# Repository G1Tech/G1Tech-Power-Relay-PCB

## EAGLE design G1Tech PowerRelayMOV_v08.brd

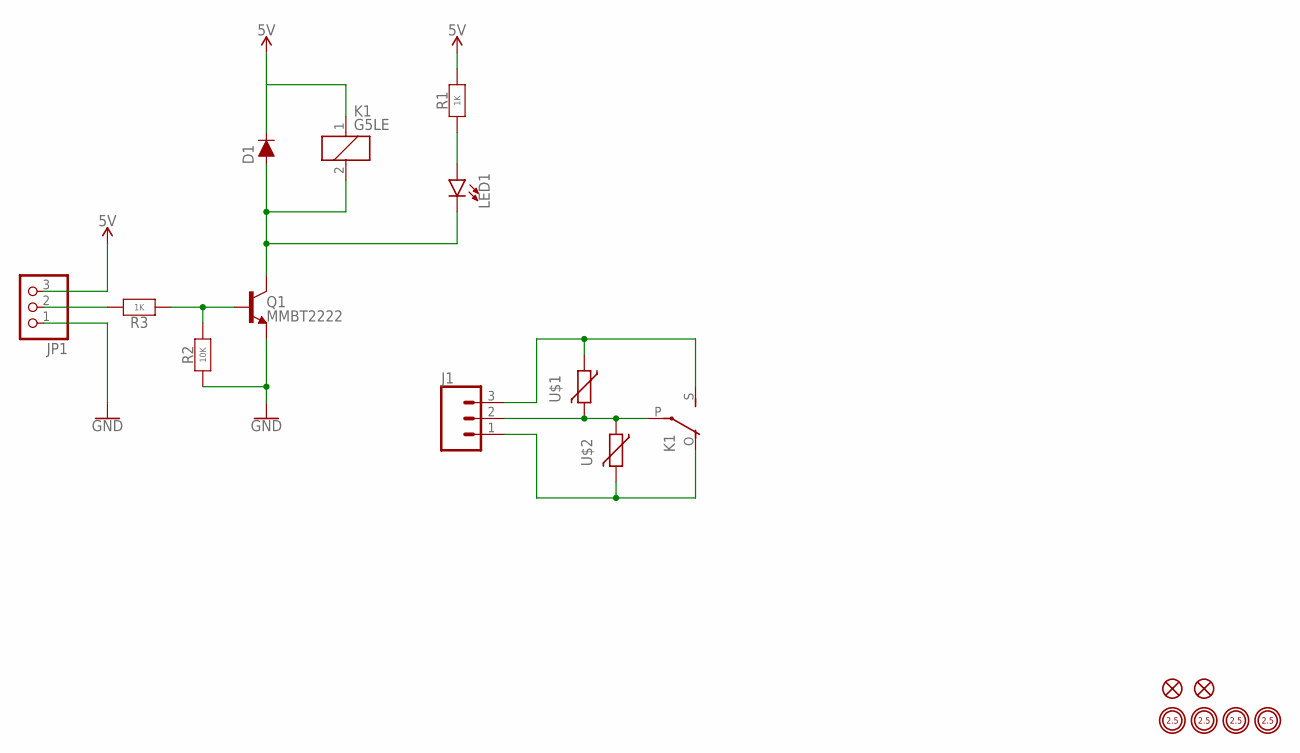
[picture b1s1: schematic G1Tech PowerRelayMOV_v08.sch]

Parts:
D1: DIODE-1N4148W; SOD123
FD1, FD2: FIDUCIAL-1X2
H1, H2, H3, H4: MOUNTINGHOLE-PLATED-2.5
J1: CONN_03-SCREW-5MM; SCREWTERMINAL-5MM-3
JP1: PINHD-1X3; 1X03
K1: G5LE
LED1: LED0805
Q1: MMBT2222; SOT23-3
R1, R3: 1K; YAGEO-R0603
R2: 10K; YAGEO-R0603
U$1, U$2: MOV-V250LA4P; V250LA4P

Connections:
5V: D1.C, JP1.3, K1.1, R1.2
GND: JP1.1, Q1.2 (E), R2.1
unnamed: D1.A, K1.2, LED1.C, Q1.3 (C)
unnamed: LED1.A, R1.1
unnamed: Q1.1 (B), R2.2, R3.1
unnamed: JP1.2, R3.2
unnamed: J1.2, K1.P, U$1.P$2 (2), U$2.P$1 (1)
unnamed: J1.3, K1.S, U$1.P$1 (1)
unnamed: J1.1, K1.O, U$2.P$2 (2)

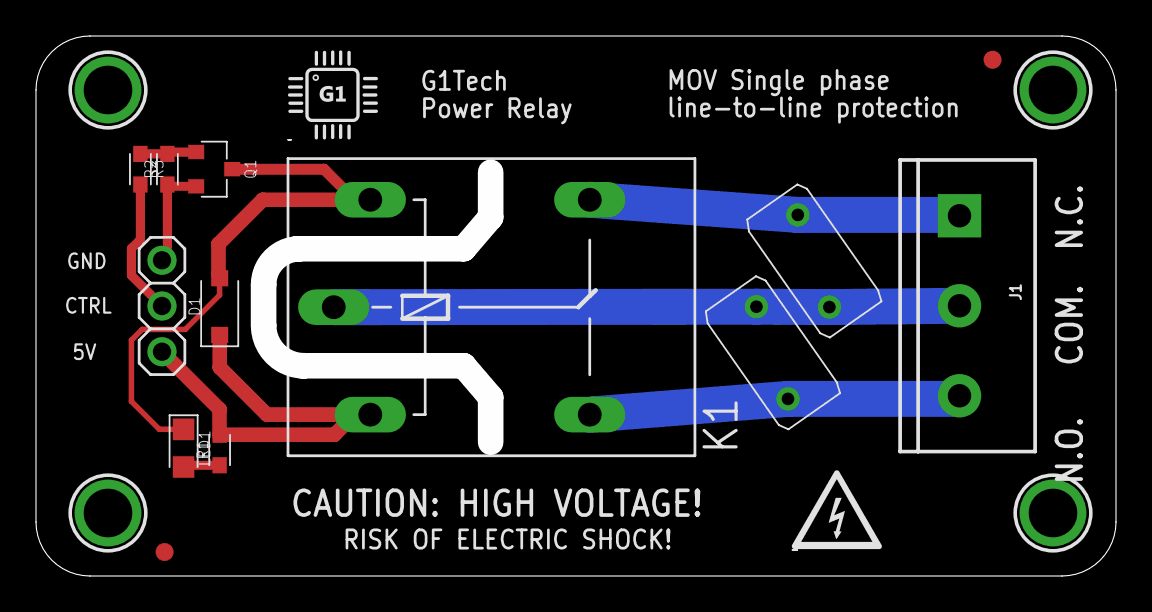
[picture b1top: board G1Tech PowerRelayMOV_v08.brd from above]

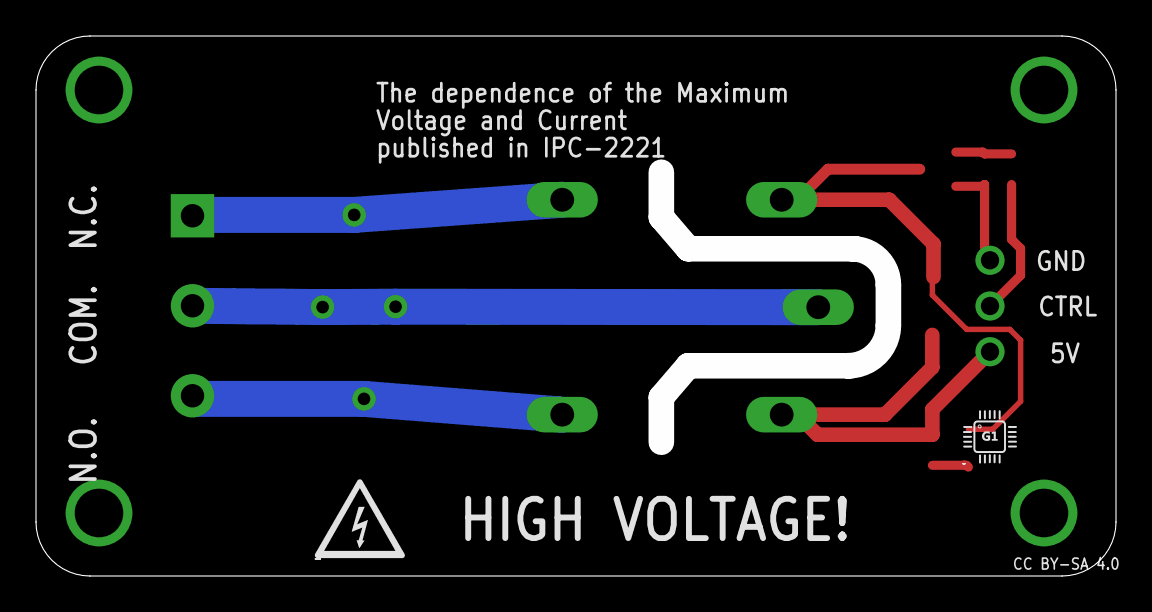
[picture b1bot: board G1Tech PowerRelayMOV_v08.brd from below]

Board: 2 copper layers, 60.0 x 30.0 mm, 21 parts (2 on the bottom side), 9 nets.

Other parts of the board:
U$5: G1TECH-LOGO-5MM
U$7, U$8: LOGO-HIGH-VOLTAGE-5MM
U$9: LOGO-G1TECH-3MM

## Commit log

2018-05-03 :confetti_ball: Added .gitattributes & .gitignore files

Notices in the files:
G1Tech PowerRelayMOV_v08.brd:
CC BY-SA 4.0
parts and their libraries:
SparkFun-Connectors: Licensing: Creative Commons ShareAlike 4.0 International - https://creativecommons.org/licenses/by-sa/4.0
